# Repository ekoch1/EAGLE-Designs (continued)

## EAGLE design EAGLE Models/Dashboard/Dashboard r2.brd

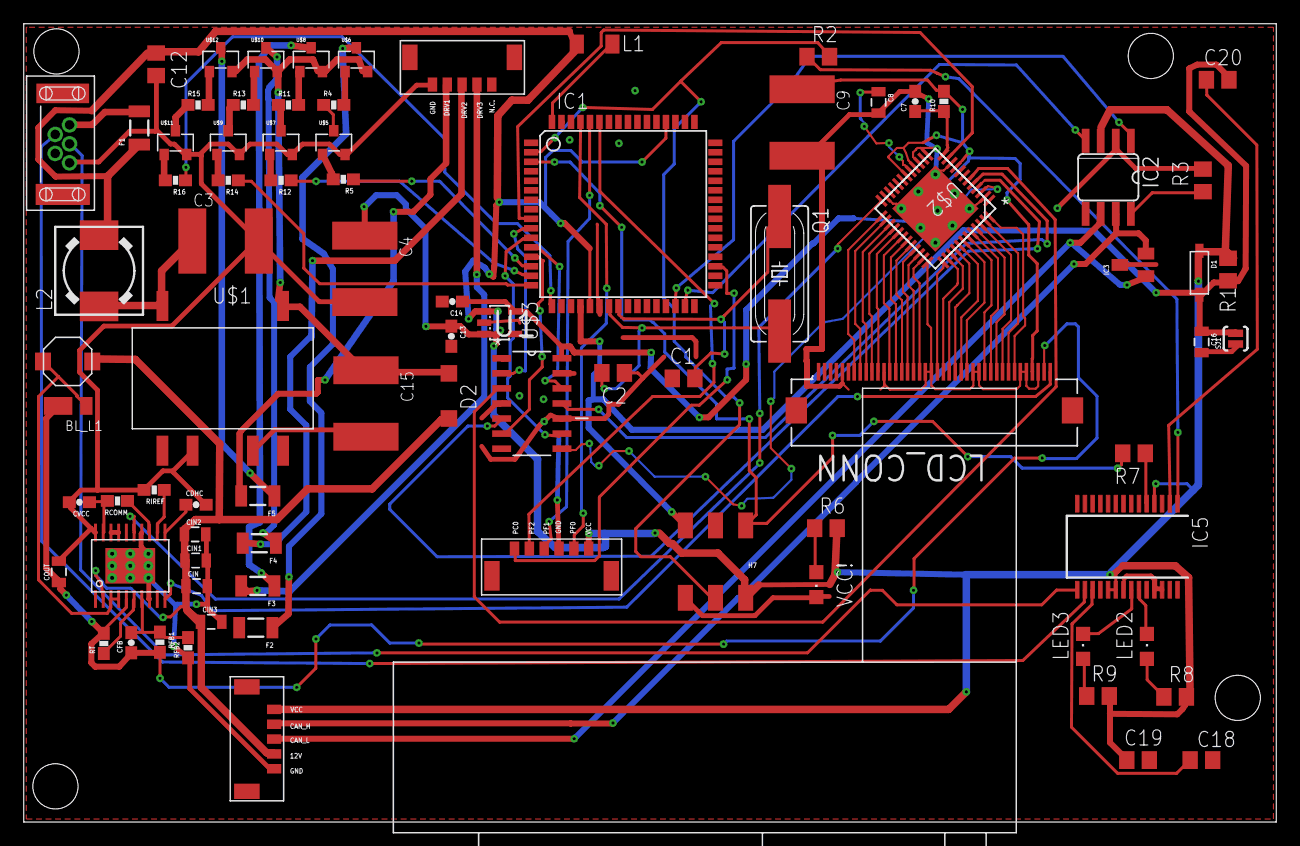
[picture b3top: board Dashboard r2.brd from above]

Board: 2 copper layers, 105.5 x 67.2 mm, 84 parts (0 on the bottom side), 100 nets.

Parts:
BL_D1: DFLS1100-7; POWERDI-123
BL_L1: 47uH; 2-SMD
C1, C2: 18pF; C0805
C3, C4: 22uF; C2220
C7: 100nF; 0603-CAP
C8: 4.7uF; 0805
C9, C15: 10uF; C2220
C12, C18, C19, C20: 100n; C0805
C13, C14: 1uF; 0603-CAP
C16: 4.7nF; 0805
CANPWR: MICRO5LOCK
CDHC: 390nF; 0603-CAP
CFB: 10.0pF; 0603-CAP
CIN, CIN1, CIN2, CIN3: 4.7uF; 0805
COUT: 120nF; 0805
CVCC: 1uF; 0603-CAP
D1: 1N4148; SOD-123
D2: 1N5819; SOD123
F1: 16V,0.25A; PTC-1206
F2, F3, F4, F5: 15V,0.5A; PTC-1206
H7: ICSP; 2X3_SMD_FCI_54202-G30
IC1: AT90CAN128; TQFP64
IC2: MCP2551SO8; SO08
IC3: NUP2105L; SOT-23
IC5: FT232RL; SSOP28
L1: CS321613-100K; L3216C
L2: 22uH; DR73
LCD_CONN: FH12A-40S-0.5SH(55); HIROSE_FH12A-40S-0.5SH(55)
LED2: RX; CHIPLED_0805
LED3: TX; CHIPLED_0805
LEDOUT: MICRO5LOCK
Q1: 56P2859; HC49UP
R1, R3: 100K; R0805
R2, R7, R8, R9: 1k; R0805
R4, R5, R11, R12, R13, R14, R15, R16: 0603-RES
R6: 1K; R0805
R10: 47k; 0603-RES
RCOMM: 52.3k; 0603-RES
RFB1: 309k; 0603-RES
RFB2: 16.2k; 0603-RES
RIREF: 20.5k; 0603-RES
ROT/PUSH: MICRO6LOCK
RT: 226k; 0603-RES
SJ1: SOLDERJUMPERNO; SJ_2S-NO
U1: 74LCX125M; SOIC127P600X175-14N
U$1: V7805-1000; V78XX-1000
U$2: FT801; RGZ48_5P15X5P15
U$3: LP5907-3.3; SOT23-DBV
U$4: LM3492HC; PWP0020A
U$5, U$7, U$9, U$11: MMBT4401-7-F; SOT-23-3
U$6, U$8, U$10, U$12: MMBT4403-7-F; SOT-23-3
U$13: TCG043WQLBAANN-GN00; TCG043WQLBAANN
U$14: MUSBB
VCC!: PWR; CHIPLED_0805

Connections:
3.3V: C9.1, C14.1, LCD_CONN.P4, R10.2, U1.14, U$2.9, U$2.16, U$2.18, U$3.5
12V: BL_L1.1, CANPWR.P2, CIN.1, CIN1.1, CIN2.1, CIN3.1, D2.A, U$4.2
12V_PROTECTED: C15.1, D2.C, U$1.1, U$6.P$3, U$8.P$3, U$10.P$3, U$12.P$3
AVR_CS: IC1.10, U1.2
AVR_MISO: IC1.13, U1.6
AVR_MOSI: IC1.12, U1.12
AVR_SCLK: IC1.11, U1.9
B2: LCD_CONN.P23, U$2.35
B3: LCD_CONN.P24, U$2.34
B4: LCD_CONN.P25, U$2.33
B5: LCD_CONN.P26, U$2.32
B6: LCD_CONN.P27, U$2.31
B7: LCD_CONN.P28, U$2.30
BACKLIGHT_CTRL: U$2.24, U$4.15
BL_ANODE: BL_D1.C, CFB.1, COUT.1, LCD_CONN.P2, RFB1.2, RT.2, U$4.5
BL_CATHODE: LCD_CONN.P1, U$4.10
CAN_H: CANPWR.P4, IC2.7, IC3.2
CAN_L: CANPWR.P3, IC2.6, IC3.1
D+: IC5.15, U$14.P3
D-: IC5.16, U$14.P2
DATA_EN: LCD_CONN.P34, U$2.25
DCLK: LCD_CONN.P30, U$2.29
DISP_EN: LCD_CONN.P31, U$2.28
DRV1: F5.2, LEDOUT.P2
DRV2: F4.2, LEDOUT.P3
DRV3: F3.2, LEDOUT.P4
DTR: C20.1, IC5.2
FT801_CS_N: U1.3, U$2.6
FT801_MISO: U1.5, U$2.4
FT801_MOSI: U1.11, U$2.5
FT801_SCLK: U1.8, U$2.3
G2: LCD_CONN.P15, U$2.42
G3: LCD_CONN.P16, U$2.41
G4: LCD_CONN.P17, U$2.40
G5: LCD_CONN.P18, U$2.39
G6: LCD_CONN.P19, U$2.38
G7: LCD_CONN.P20, U$2.37
GND: C1.1, C2.1, C3.2, C4.2, C7.2, C8.2, C9.2, C12.2, C13.2, C14.2, C15.2, C16.2, C18.2, C19.2, CANPWR.P1, CDHC.2, CIN.2, CIN1.2, CIN2.2, CIN3.2, COUT.2, CVCC.2, H7.6, IC1.22, IC1.53, IC1.63, IC2.2, IC3.3, IC5.7, IC5.18, IC5.21, IC5.25, IC5.26, LCD_CONN.P3, LCD_CONN.P5, LCD_CONN.P6, LCD_CONN.P13, LCD_CONN.P14, LCD_CONN.P21, LCD_CONN.P22, LCD_CONN.P29, LCD_CONN.P36, LEDOUT.P1, R3.2, RFB2.1, RIREF.2, ROT/PUSH.P4, SJ1.1, U1.1, U1.4, U1.10, U1.13, U$1.7, U$1.9, U$2.2, U$2.10, U$2.13, U$2.15, U$2.23, U$2.36, U$2.EP, U$2.V_1, U$2.V_2, U$2.V_3, U$2.V_4, U$2.V_5, U$2.V_6, U$2.V_7, U$2.V_8, U$2.V_9, U$3.2, U$4.8, U$4.14, U$4.17, U$4.18, U$4.20, U$4.EP, U$4.P$1, U$4.P$2, U$4.P$3, U$4.P$4, U$4.P$5, U$4.P$6, U$4.P$7, U$4.P$8, U$4.P$9, U$5.P$3, U$7.P$3, U$9.P$3, U$11.P$3, U$14.P5, VCC!.C
HSYNC: LCD_CONN.P32, U$2.27
INT_N: IC1.9, U$2.11
M8RXD: IC5.1, R2.1
M8TXD: IC5.5, R7.1
unnamed: C8.1, U$2.17
unnamed: C7.1, R10.1, U$2.12
unnamed: CVCC.1, RCOMM.2, U$4.19
unnamed: RCOMM.1, U$4.13
unnamed: IC2.8, R3.1
unnamed: CDHC.1, U$4.11
unnamed: BL_D1.A, BL_L1.2, U$4.3, U$4.4
unnamed: R6.1, VCC!.A
unnamed: CFB.2, RFB1.1, RFB2.2, U$4.7
unnamed: C1.2, IC1.24, Q1.1
unnamed: RT.1, U$4.6
unnamed: C3.1, L2.1, U$1.5
unnamed: RIREF.1, U$4.12
unnamed: IC1.64, L1.2
unnamed: R5.2, U$5.P$2
unnamed: R4.2, U$6.P$2
unnamed: R4.1, U$5.P$1
unnamed: F2.1, U$6.P$1
unnamed: R12.2, U$7.P$2
unnamed: R11.2, U$8.P$2
unnamed: R11.1, U$7.P$1
unnamed: F3.1, U$8.P$1
unnamed: R14.2, U$9.P$2
unnamed: IC5.23, LED2.C
unnamed: R13.2, U$10.P$2
unnamed: IC5.22, LED3.C
unnamed: LED2.A, R8.1
unnamed: LED3.A, R9.1
unnamed: R13.1, U$9.P$1
unnamed: F4.1, U$10.P$1
unnamed: R16.2, U$11.P$2
unnamed: R15.2, U$12.P$2
unnamed: R15.1, U$11.P$1
unnamed: F5.1, U$12.P$1
PB4(PWM): IC1.14, R5.1
PB5(PWM): IC1.15, R12.1
PB6(PWM): IC1.16, R14.1
PB7(PWM): IC1.17, R16.1
PC0: IC1.35, ROT/PUSH.P1
PF0: IC1.61, ROT/PUSH.P5
PF1: IC1.60, ROT/PUSH.P3
PF2: IC1.59, ROT/PUSH.P2
R2: LCD_CONN.P7, U$2.48
R3: LCD_CONN.P8, U$2.47
R4: LCD_CONN.P9, U$2.46
R5: LCD_CONN.P10, U$2.45
R6: LCD_CONN.P11, U$2.44
R7: LCD_CONN.P12, U$2.43
RESET: C16.1, C20.2, D1.A, H7.5, IC1.20, R1.1, SJ1.2
RX: H7.4, IC1.2, R2.2
RXCAN: IC1.31, IC2.4
TX: H7.1, IC1.3, R7.2
TXCAN: IC1.30, IC2.1
USB_V_IN: F1.2, U$14.P1
VCC: C4.1, C12.1, C13.1, C19.1, CANPWR.P5, D1.C, F1.1, H7.2, IC1.21, IC1.52, IC2.3, IC5.4, IC5.19, IC5.20, L1.1, L2.2, R1.2, R6.2, R8.2, R9.2, ROT/PUSH.P6, U$3.1, U$3.3
VCC3O: C18.1, IC5.17
VSYNC: LCD_CONN.P33, U$2.26
XTAL1: C2.2, IC1.23, Q1.2

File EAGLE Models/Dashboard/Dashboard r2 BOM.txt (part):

Partlist exported from C:/Users/Daniel Baron/Desktop/FSAE2016Boards and Schematics/Dashboard12-12.sch at 1/12/2016 12:52 PM

Part     Value               Device              Package                    Description                                                                         MPN                 OC_FARNELL OC_NEWARK PACKAGE                           SUPPLIER 
BL_D1    DFLS1100-7          DFLS1100-7          POWERDI-123                                                                                                                                                                                        
BL_L1    47uH                LTF4022-D           2-SMD                      LTF4022                                                                                                                                                                 
C1       18pF                C-USC0805           C0805                      CAPACITOR, American symbol                                                                                                                                              
C2       18pF                C-USC0805           C0805                      CAPACITOR, American symbol                                                                                                                                              
C3       22uF                C-USC2220           C2220                      CAPACITOR, American symbol                                                                                                                                              
C4       22uF                C-USC2220           C2220                      CAPACITOR, American symbol                                                                                                                                              
C7       100nF               CAP0603-CAP         0603-CAP                   Capacitor                                                                                                                                                               
C8       4.7uF               CAP0805             0805                       Capacitor                                                                                                                                                               
C9       10uF                C-USC2220           C2220                      CAPACITOR, American symbol                                                                                                                                              
C12      100n                C-USC0805           C0805                      CAPACITOR, American symbol                                                                                                                                              
C13      1uF                 CAP0603-CAP         0603-CAP                   Capacitor                                                                                                                                                               
C14      1uF                 CAP0603-CAP         0603-CAP                   Capacitor                                                                                                                                                               
C15      10uF                C-USC2220           C2220                      CAPACITOR, American symbol                                                                                                                                              
C16      4.7nF               CAP0805             0805                       Capacitor                                                                                                                                                               
C18      100n                C-USC0805           C0805                      CAPACITOR, American symbol                                                                                                                                              
C19      100n                C-USC0805           C0805                      CAPACITOR, American symbol                                                                                                                                              
C20      100n                C-USC0805           C0805                      CAPACITOR, American symbol                                                                                                                                              
CANPWR   MICRO5LOCK          MICRO5LOCK          MICRO5LOCK                                                                                                                                                                                         
CDHC     390nF               CAP0603-CAP         0603-CAP                   Capacitor                                                                                                                                                               
CFB      10.0pF              CAP0603-CAP         0603-CAP                   Capacitor                                                                                                                                                               
CIN      4.7uF               CAP0805             0805                       Capacitor                                                                                                                                                               
CIN1     4.7uF               CAP0805             0805                       Capacitor                                                                                                                                                               
CIN2     4.7uF               CAP0805             0805                       Capacitor                                                                                                                                                               
CIN3     4.7uF               CAP0805             0805                       Capacitor                                                                                                                                                               
COUT     120nF               CAP0805             0805                       Capacitor                                                                                                                                                               
CVCC     1uF                 CAP0603-CAP         0603-CAP                   Capacitor                                                                                                                                                               
D1       1N4148              DIODESOD-123        SOD-123                    Diode                                                                                                                                                                   
D2       1N5819              1N5819-BSOD123      SOD123                     1.0A SCHOTTKY BARRIER RECTIFIER                                                                                                                                         
F1       16V,0.25A           PTCSMD              PTC-1206                   Resettable Fuse PTC                                                                                                                                                     
F2       15V,0.5A            PTCSMD              PTC-1206                   Resettable Fuse PTC                                                                                                                                                     
F3       15V,0.5A            PTCSMD              PTC-1206                   Resettable Fuse PTC                                                                                                                                                     
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
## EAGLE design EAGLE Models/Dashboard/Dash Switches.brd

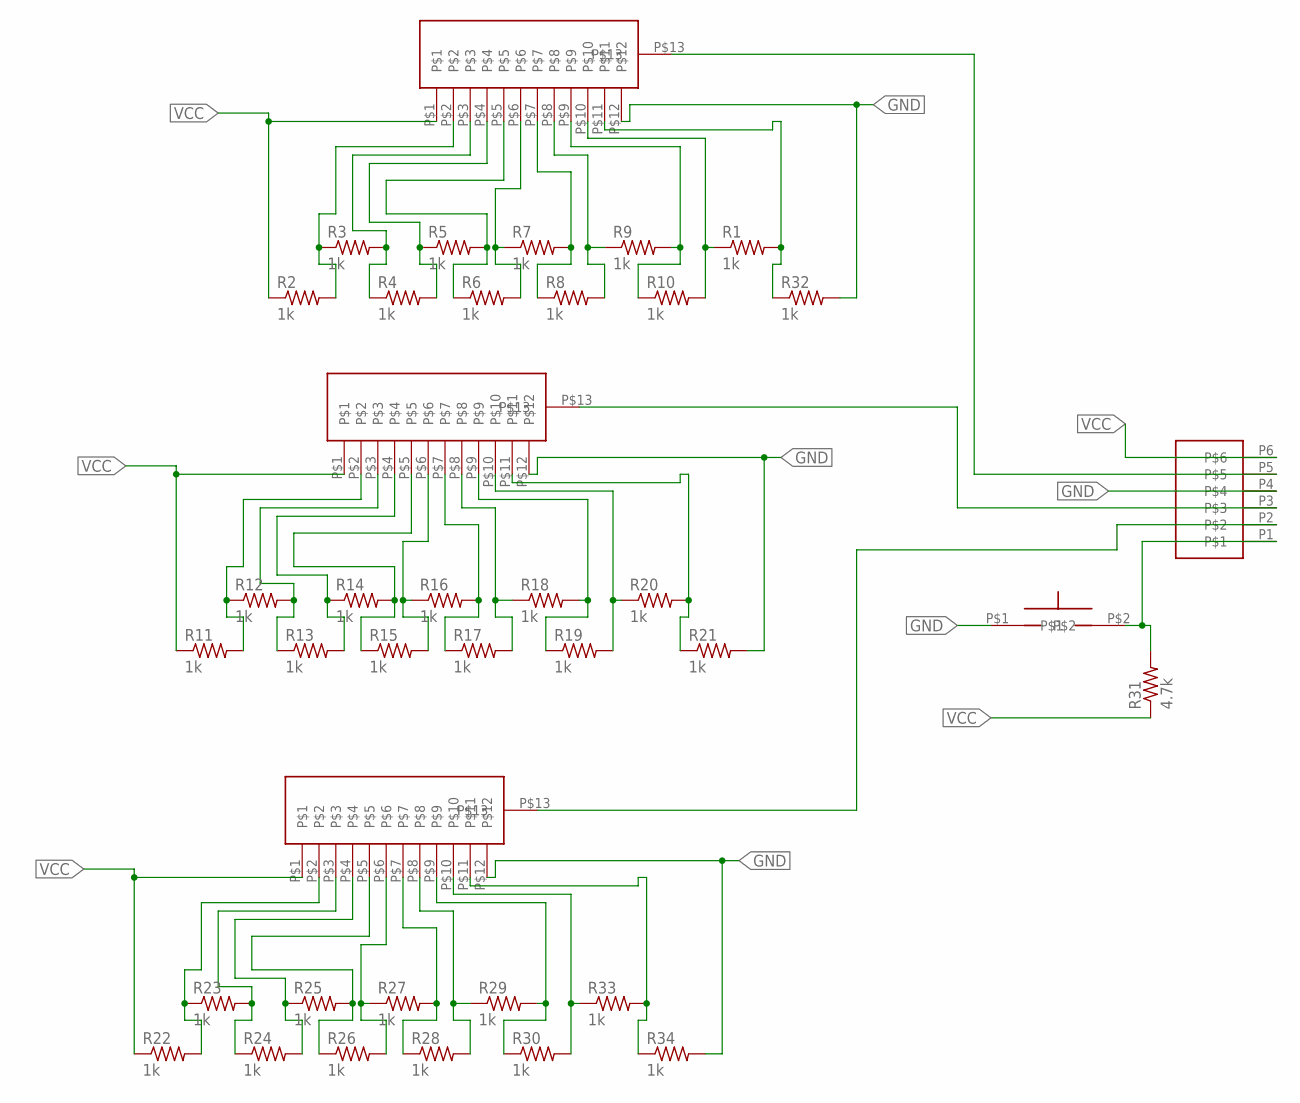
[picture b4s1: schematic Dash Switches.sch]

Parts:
R1, R2, R3, R4, R5, R6, R7, R8, R9, R10, R11, R12, R13, R14, R15, R16, R17, R18, R19, R20, R21, R22, R23, R24, R25, R26, R27, R28, R29, R30, R32, R33, R34: 1k; R0603
R31: 4.7k; R0603
U$1, U$2, U$3: ROTSWITCH
U$5: PUSH
U$6: MICRO6LOCK

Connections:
GND: R21.2, R32.2, R34.2, U$1.P$12, U$2.P$12, U$3.P$12, U$5.P$1, U$6.P4
unnamed: R1.1, R10.2, U$1.P$10
unnamed: R2.2, R3.1, U$1.P$2
unnamed: R3.2, R4.1, U$1.P$3
unnamed: R4.2, R5.1, U$1.P$4
unnamed: R5.2, R6.1, U$1.P$5
unnamed: R11.2, R12.1, U$2.P$2
unnamed: R12.2, R13.1, U$2.P$3
unnamed: R8.2, R9.1, U$1.P$8
unnamed: R9.2, R10.1, U$1.P$9
unnamed: R13.2, R14.1, U$2.P$4
unnamed: R6.2, R7.1, U$1.P$6
unnamed: R7.2, R8.1, U$1.P$7
unnamed: R14.2, R15.1, U$2.P$5
unnamed: R17.2, R18.1, U$2.P$8
unnamed: R18.2, R19.1, U$2.P$9
unnamed: R15.2, R16.1, U$2.P$6
unnamed: R16.2, R17.1, U$2.P$7
unnamed: R19.2, R20.1, U$2.P$10
unnamed: U$2.P$13, U$6.P3
unnamed: R20.2, R21.1, U$2.P$11
unnamed: R22.2, R23.1, U$3.P$2
unnamed: R23.2, R24.1, U$3.P$3
unnamed: R24.2, R25.1, U$3.P$4
unnamed: R25.2, R26.1, U$3.P$5
unnamed: R28.2, R29.1, U$3.P$8
unnamed: R29.2, R30.1, U$3.P$9
unnamed: R26.2, R27.1, U$3.P$6
unnamed: R27.2, R28.1, U$3.P$7
unnamed: R30.2, R33.1, U$3.P$10
unnamed: U$3.P$13, U$6.P2
unnamed: R33.2, R34.1, U$3.P$11
unnamed: U$1.P$13, U$6.P5
unnamed: R31.2, U$5.P$2, U$6.P1
unnamed: R1.2, R32.1, U$1.P$11
VCC: R2.1, R11.1, R22.1, R31.1, U$1.P$1, U$2.P$1, U$3.P$1, U$6.P6

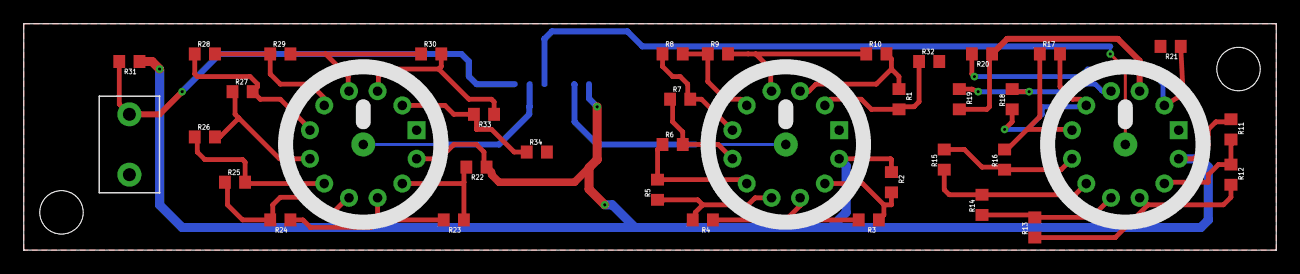
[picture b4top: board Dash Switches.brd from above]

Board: 2 copper layers, 105.4 x 19.1 mm, 39 parts (1 on the bottom side), 36 nets.

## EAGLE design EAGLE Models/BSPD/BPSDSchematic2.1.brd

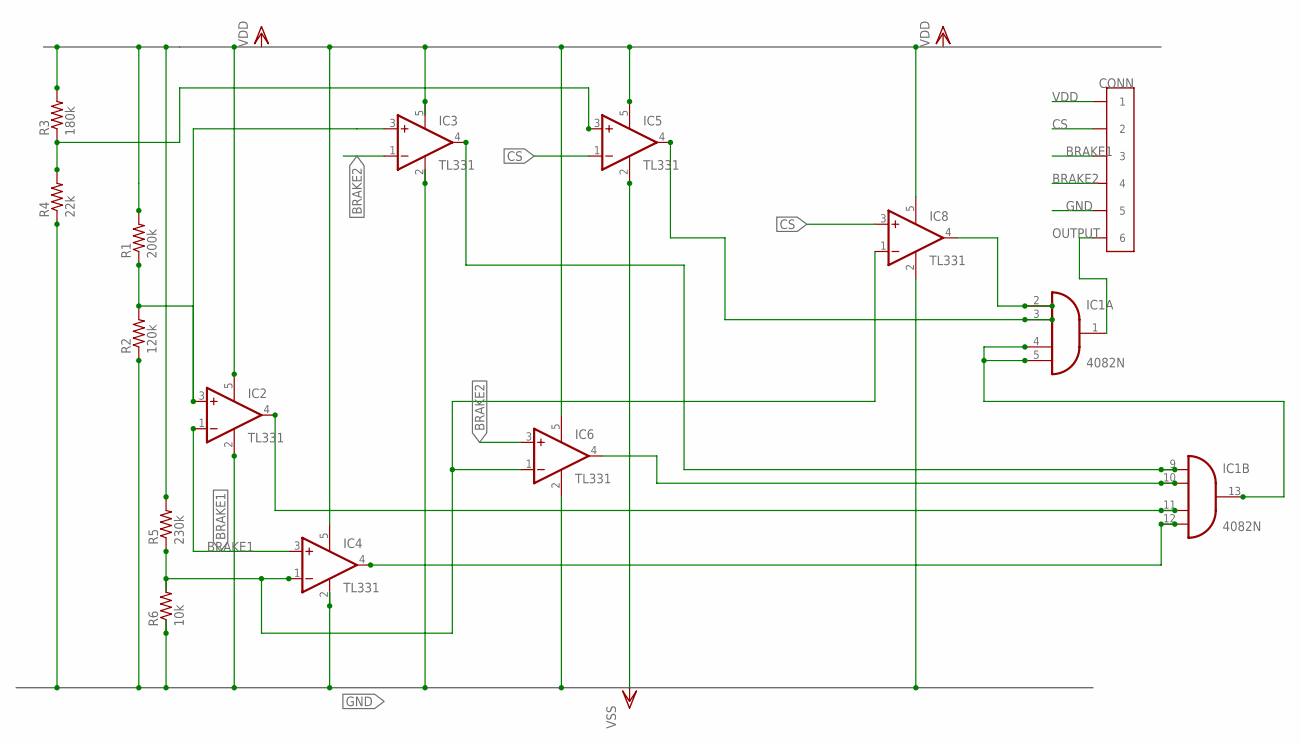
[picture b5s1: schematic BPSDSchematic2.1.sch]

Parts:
CONN: CONN_6; CONNECTOR_6
IC1: 4082N; DIL14
IC2, IC3, IC4, IC5, IC6, IC8: TL331; DBV-R-PDSO-G5
R1: 200k; 0207/15
R2: 120k; 0207/15
R3: 180k; 0207/15
R4: 22k; 0207/15
R5: 230k; 0207/15
R6: 10k; 0207/15

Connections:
BRAKE1: CONN.5 (3), CONN.6 (3), IC2.1 (-IN), IC4.3 (+IN)
BRAKE2: CONN.7 (4), CONN.8 (4), IC3.1 (-IN), IC6.3 (+IN)
CS: CONN.3 (2), CONN.4 (2), IC5.1 (-IN), IC8.3 (+IN)
GND: CONN.9 (5), CONN.10 (5), IC1.7 (VSS), IC2.2 (GND), IC3.2 (GND), IC4.2 (GND), IC5.2 (GND), IC6.2 (GND), IC8.2 (GND), R2.1, R4.1, R6.1
unnamed: IC1.12 (I3), IC4.4 (OUT)
unnamed: IC1.11 (I2), IC2.4 (OUT)
unnamed: IC1.10 (I1), IC6.4 (OUT)
unnamed: IC1.9 (I0), IC3.4 (OUT)
unnamed: IC1.2 (I0), IC8.4 (OUT)
unnamed: IC1.4 (I2), IC1.5 (I3), IC1.13 (O)
unnamed: IC2.3 (+IN), IC3.3 (+IN), R1.1, R2.2
unnamed: IC4.1 (-IN), IC6.1 (-IN), IC8.1 (-IN), R5.1, R6.2
unnamed: IC5.3 (+IN), R3.1, R4.2
unnamed: IC1.3 (I1), IC5.4 (OUT)
OUTPUT: CONN.11 (6), CONN.12 (6), IC1.1 (O)
VDD: CONN.1, CONN.2 (1), IC1.14 (VDD), IC2.5 (V+), IC3.5 (V+), IC4.5 (V+), IC5.5 (V+), IC6.5 (V+), IC8.5 (V+), R1.2, R3.2, R5.2

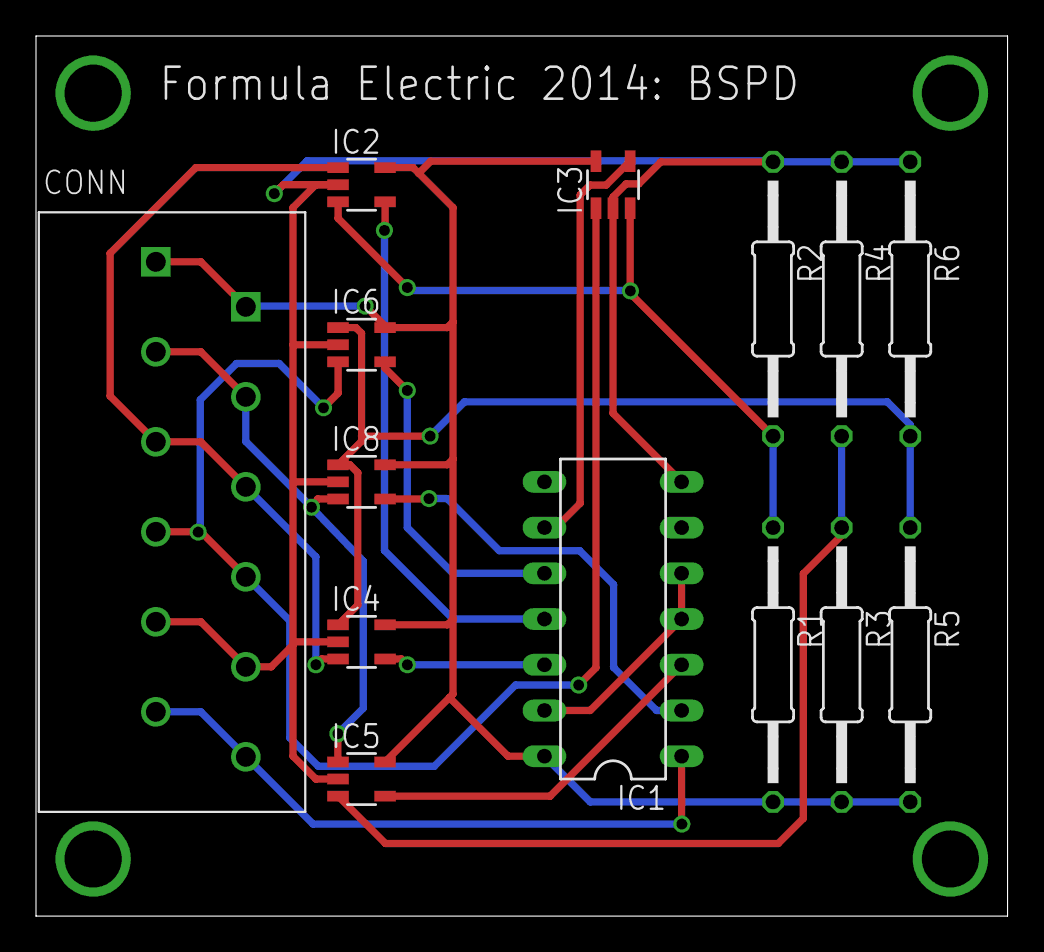
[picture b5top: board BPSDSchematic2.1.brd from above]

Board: 2 copper layers, 54.0 x 48.9 mm, 14 parts (0 on the bottom side), 16 nets.

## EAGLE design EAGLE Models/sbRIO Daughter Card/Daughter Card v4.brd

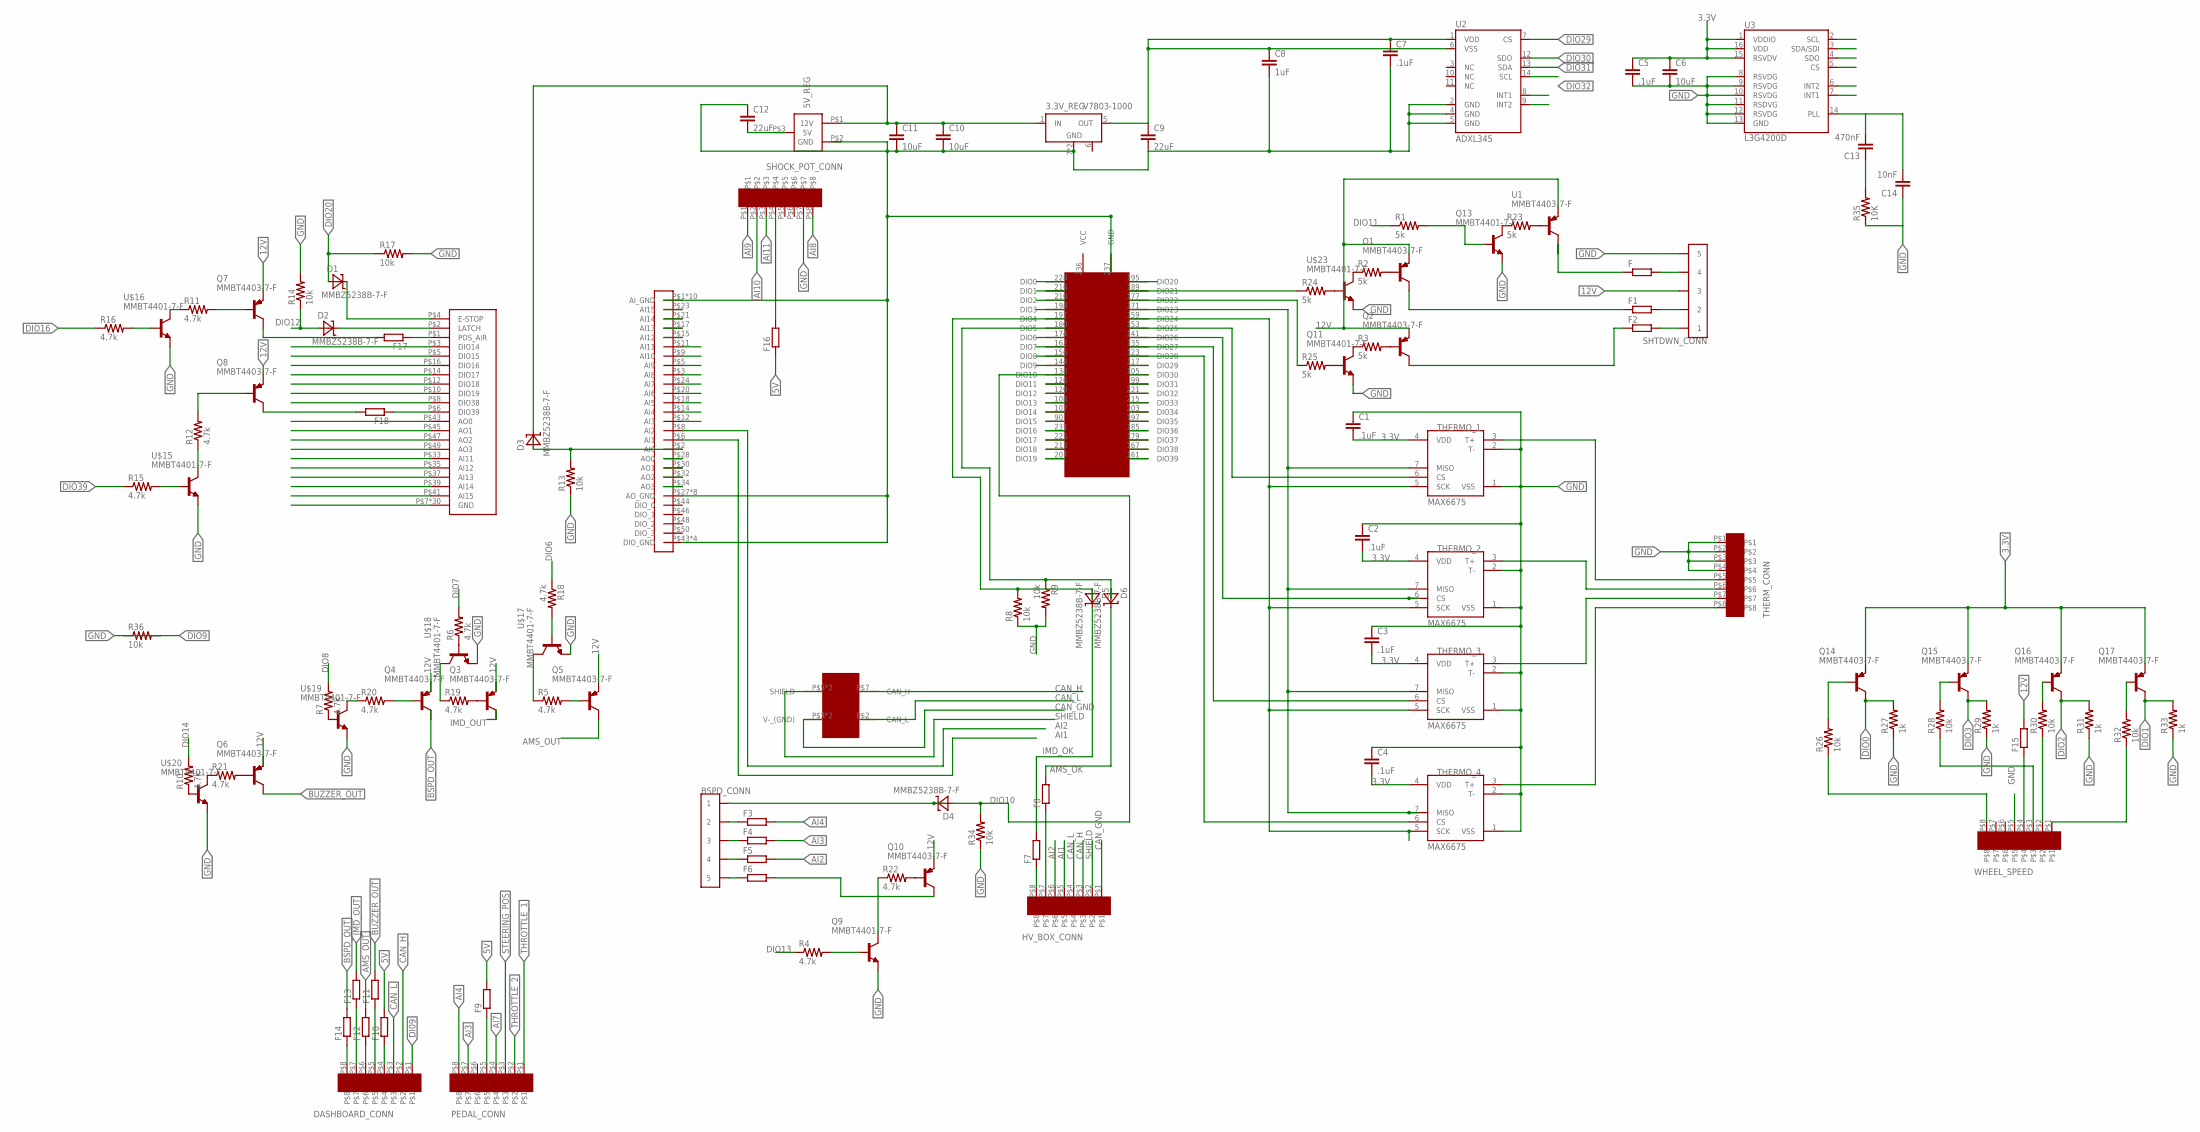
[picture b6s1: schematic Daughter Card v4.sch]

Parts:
3.3V_REG: V7803-1000; V78XX-1000
5V_REG: V78XX-1500; V78XX-1500R
BSPD_CONN: CONN_5; CONNECTOR_5
C1, C2, C3, C4, C5, C7: .1uF; 0603-CAP
C6, C10, C11: 10uF; 0603-CAP
C8: 1uF; 0603-CAP
C9, C12: 22uF; 0603-CAP
C13: 470nF; 0603-CAP
C14: 10nF; 0603-CAP
D1, D2, D3, D4, D5, D6: MMBZ5238B-7-F; SOT-23-3
DASHBOARD_CONN: EN3_PCB_8
F, F1, F2, F3, F4, F5, F6, F7, F8, F9, F10, F11, F12, F13, F14, F15, F16, F17, F18: R-EU_R0402; R0402
HV_BOX_CONN: EN3_PCB_8
PEDAL_CONN: EN3_PCB_8
Q1, Q2, Q3, Q4, Q5, Q6, Q7, Q8, Q10, Q14, Q15, Q16, Q17: MMBT4403-7-F; SOT-23-3
Q9, Q11, Q13: MMBT4401-7-F; SOT-23-3
R1, R2, R3, R23, R24, R25: 5k; R0402
R4, R5, R6, R7, R10, R11, R12, R15, R16, R18, R19, R20, R21, R22: 4.7k; R0402
R8, R9, R13, R14, R17, R26, R28, R30, R32, R34, R36: 10k; R0402
R27, R29, R31, R33: 1k; R0402
R35: 10K; 0603-RES
SBRIO_ANALOG: SBRIO_MIO; SBRIO_J502_J503
SBRIO_AUX: SBRIO_AUX; SBRIO_J502_J503
SHOCK_POT_CONN: EN3_PCB_8
SHTDWN_CONN: CONN_5; CONNECTOR_5
THERMO_1, THERMO_2, THERMO_3, THERMO_4: MAX6675; SO08
THERM_CONN: EN3_PCB_8
U1: MMBT4403-7-F; SOT-23-3
U2: ADXL345; LGA14
U3: L3G4200D; LGA16-4X4
U$2: SBRIO_W500; SBRIO_W
U$3: SBRIO_RMC; SEAM-40-XX.X-XX-06-X-A
U$15, U$16, U$17, U$18, U$19, U$20, U$23: MMBT4401-7-F; SOT-23-3
WHEEL_SPEED: EN3_PCB_8

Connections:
3.3V: 3.3V_REG.5 (OUT), C1.2, C2.2, C3.2, C4.2, C5.1, C6.1, C7.1, C8.1, C9.1, Q14.P$3 (E), Q15.P$3 (E), Q16.P$3 (E), Q17.P$3 (E), THERMO_1.4 (VDD), THERMO_2.4 (VDD), THERMO_3.4 (VDD), THERMO_4.4 (VDD), U2.1 (VDD), U2.6 (VSS), U3.1 (VDDIO), U3.15 (RSVDV), U3.16 (VDD)
5V: 5V_REG.P$3 (5V), C12.2, F9.2, F10.2, F16.1
12V: 3.3V_REG.1 (IN), 5V_REG.P$1 (12V), C10.1, C11.1, D3.P$1 (C), F15.2, Q1.P$3 (E), Q2.P$3 (E), Q3.P$3 (E), Q4.P$3 (E), Q5.P$3 (E), Q6.P$3 (E), Q7.P$3 (E), Q8.P$3 (E), Q10.P$3 (E), SHTDWN_CONN.5 (3), SHTDWN_CONN.6 (3), U1.P$3 (E)
AI1: HV_BOX_CONN.P$5, SBRIO_ANALOG.P$6 (AI1)
AI2: F5.2, HV_BOX_CONN.P$6, SBRIO_ANALOG.P$8 (AI2)
AI3: F4.2, PEDAL_CONN.P$7, SBRIO_ANALOG.P$12 (AI3)
AI4: F3.2, PEDAL_CONN.P$8, SBRIO_ANALOG.P$14 (AI4)
AI7: PEDAL_CONN.P$4, SBRIO_ANALOG.P$24 (AI7)
AI8: SBRIO_ANALOG.P$3 (AI8), SHOCK_POT_CONN.P$8
AI9: SBRIO_ANALOG.P$5 (AI9), SHOCK_POT_CONN.P$1
AI10: SBRIO_ANALOG.P$9 (AI10), SHOCK_POT_CONN.P$2
AI11: SBRIO_ANALOG.P$11 (AI11), SBRIO_AUX.P$33 (AI11), SHOCK_POT_CONN.P$3
AI12: SBRIO_ANALOG.P$15 (AI12), SBRIO_AUX.P$35 (AI12)
AI13: SBRIO_ANALOG.P$17 (AI13), SBRIO_AUX.P$37 (AI13)
AI15: SBRIO_ANALOG.P$23 (AI15), SBRIO_AUX.P$41 (AI15)
AMS_OK: D6.P$1 (C), F8.2
AMS_OUT: F12.2, Q5.P$1 (C)
AO0: SBRIO_ANALOG.P$28 (AO0), SBRIO_AUX.P$43 (AO0)
AO1: SBRIO_ANALOG.P$30 (AO1), SBRIO_AUX.P$45 (AO1)
AO2: SBRIO_ANALOG.P$32 (AO2), SBRIO_AUX.P$47 (AO2)
AO3: SBRIO_ANALOG.P$34 (AO3), SBRIO_AUX.P$49 (AO3)
BSPD_OUT: F14.2, Q4.P$1 (C)
BUZZER_OUT: F11.2, Q6.P$1 (C)
CAN_GND: HV_BOX_CONN.P$1, U$2.P$3 (V-_(GND)), U$2.P$6 (V-_(GND))
CAN_H: DASHBOARD_CONN.P$2, HV_BOX_CONN.P$3, U$2.P$7 (CAN_H)
CAN_L: DASHBOARD_CONN.P$3, HV_BOX_CONN.P$4, U$2.P$2 (CAN_L)
DI09: DASHBOARD_CONN.P$1
DIO0: Q14.P$1 (C), R27.2, U$3.228 (DIO0)
DIO1: Q17.P$1 (C), R33.2, U$3.216 (DIO1)
DIO2: Q16.P$1 (C), R31.2, U$3.210 (DIO2)
DIO3: Q15.P$1 (C), R29.2, U$3.198 (DIO3)
DIO6: R18.1, U$3.174 (DIO6)
DIO7: R6.2, U$3.162 (DIO7)
DIO8: R7.2, U$3.156 (DIO8)
DIO9: R36.2, U$3.144 (DIO9)
DIO10: D4.P$2 (A), R34.2, U$3.138 (DIO10)
DIO11: R1.1, U$3.126 (DIO11)
DIO12: D2.P$2 (A), R14.1, U$3.120 (DIO12)
DIO13: R4.1, U$3.108 (DIO13)
DIO14: R10.2, SBRIO_AUX.P$3 (DIO14), U$3.102 (DIO14)
DIO15: SBRIO_AUX.P$5 (DIO15), U$3.90 (DIO15)
DIO16: R16.1, SBRIO_AUX.P$16 (DIO16), U$3.231 (DIO16)
DIO17: SBRIO_AUX.P$14 (DIO17), U$3.225 (DIO17)
DIO18: SBRIO_AUX.P$12 (DIO18), U$3.213 (DIO18)
DIO19: SBRIO_AUX.P$10 (DIO19), U$3.207 (DIO19)
DIO20: D1.P$2 (A), R17.1, U$3.195 (DIO20)
DIO29: U2.7 (CS), U$3.117 (DIO29)
DIO30: U2.12 (SDO), U3.4 (SDO), U$3.105 (DIO30)
DIO31: U2.13 (SDA), U3.3 (SDA/SDI), U$3.99 (DIO31)
DIO32: U2.14 (SCL), U3.2 (SCL), U$3.221 (DIO32)
DIO33: U3.5 (CS), U$3.215 (DIO33)
DIO34: U3.7 (INT1), U$3.203 (DIO34)
DIO35: U3.6 (INT2), U$3.197 (DIO35)
DIO36: U2.8 (INT1), U$3.185 (DIO36)
DIO37: U2.9 (INT2), U$3.179 (DIO37)
DIO38: SBRIO_AUX.P$8 (DIO38), U$3.167 (DIO38)
DIO39: R15.1, U$3.161 (DIO39)
GND: 3.3V_REG.7 (GND), 3.3V_REG.9 (GND), 5V_REG.P$2 (GND), C1.1, C2.1, C3.1, C4.1, C5.2, C6.2, C7.2, C8.2, C9.2, C10.2, C11.2, C12.1, C14.1, Q9.P$3 (E), Q11.P$3 (E), Q13.P$3 (E), R8.1, R9.2, R13.1, R14.2, R17.2, R27.1, R29.1, R31.1, R33.1, R34.1, R35.1, R36.1, SBRIO_ANALOG.P$1 (AI_GND), SBRIO_ANALOG.P$4 (AI_GND), SBRIO_ANALOG.P$7 (AI_GND), SBRIO_ANALOG.P$10 (AI_GND), SBRIO_ANALOG.P$13 (AI_GND), SBRIO_ANALOG.P$16 (AI_GND), SBRIO_ANALOG.P$19 (AI_GND), SBRIO_ANALOG.P$22 (AI_GND), SBRIO_ANALOG.P$25 (AI_GND), SBRIO_ANALOG.P$26 (AI_GND), SBRIO_ANALOG.P$27 (AO_GND), SBRIO_ANALOG.P$29 (AO_GND), SBRIO_ANALOG.P$31 (AO_GND), SBRIO_ANALOG.P$33 (AO_GND), SBRIO_ANALOG.P$35 (AO_GND), SBRIO_ANALOG.P$37 (AO_GND), SBRIO_ANALOG.P$39 (AO_GND), SBRIO_ANALOG.P$41 (AO_GND), SBRIO_ANALOG.P$43 (DIO_GND), SBRIO_ANALOG.P$45 (DIO_GND), SBRIO_ANALOG.P$47 (DIO_GND), SBRIO_ANALOG.P$49 (DIO_GND), SBRIO_AUX.P$7 (GND), SBRIO_AUX.P$9 (GND), SBRIO_AUX.P$11 (GND), SBRIO_AUX.P$13 (GND), SBRIO_AUX.P$15 (GND), SBRIO_AUX.P$17 (GND), SBRIO_AUX.P$18 (GND), SBRIO_AUX.P$19 (GND), SBRIO_AUX.P$20 (GND), SBRIO_AUX.P$21 (GND), SBRIO_AUX.P$22 (GND), SBRIO_AUX.P$23 (GND), SBRIO_AUX.P$24 (GND), SBRIO_AUX.P$25 (GND), SBRIO_AUX.P$26 (GND), SBRIO_AUX.P$27 (GND), SBRIO_AUX.P$28 (GND), SBRIO_AUX.P$29 (GND), SBRIO_AUX.P$30 (GND), SBRIO_AUX.P$31 (GND), SBRIO_AUX.P$32 (GND), SBRIO_AUX.P$34 (GND), SBRIO_AUX.P$36 (GND), SBRIO_AUX.P$38 (GND), SBRIO_AUX.P$40 (GND), SBRIO_AUX.P$42 (GND), SBRIO_AUX.P$44 (GND), SBRIO_AUX.P$46 (GND), SBRIO_AUX.P$48 (GND), SBRIO_AUX.P$50 (GND), SHOCK_POT_CONN.P$7, SHTDWN_CONN.9 (5), SHTDWN_CONN.10 (5), THERMO_1.1 (VSS), THERMO_1.2 (T-), THERMO_2.1 (VSS), THERMO_2.2 (T-), THERMO_3.1 (VSS), THERMO_3.2 (T-), THERMO_4.1 (VSS), THERMO_4.2 (T-), THERM_CONN.P$1, THERM_CONN.P$2, THERM_CONN.P$3, THERM_CONN.P$4, U2.2 (GND), U2.4 (GND), U2.5 (GND), U3.8 (RSVDG), U3.9 (RSVDG), U3.10 (RSVDG), U3.11 (RSDVG), U3.12 (RSVDG), U3.13 (GND), U$3.237 (GND), U$15.P$3 (E), U$16.P$3 (E), U$17.P$3 (E), U$18.P$3 (E), U$19.P$3 (E), U$20.P$3 (E), U$23.P$3 (E), WHEEL_SPEED.P$5
IMD_OK: D5.P$1 (C), F7.2
IMD_OUT: F13.2, Q3.P$1 (C)
unnamed: D2.P$1 (C), SBRIO_AUX.P$2 (LATCH)
unnamed: D1.P$1 (C), SBRIO_AUX.P$4 (E-STOP)
unnamed: R32.1, WHEEL_SPEED.P$1
unnamed: D3.P$2 (A), R13.2, SBRIO_ANALOG.P$2 (AI0)
unnamed: Q6.P$2 (B), R21.2
unnamed: Q16.P$2 (B), R30.2
unnamed: F1.1, Q1.P$1 (C)
unnamed: F2.1, Q2.P$1 (C)
unnamed: R28.1, WHEEL_SPEED.P$3
unnamed: R26.1, WHEEL_SPEED.P$8
unnamed: R24.1, U$3.189 (DIO21)
unnamed: R25.1, U$3.177 (DIO22)
unnamed: F8.1, HV_BOX_CONN.P$7
unnamed: F7.1, HV_BOX_CONN.P$8
unnamed: D5.P$2 (A), R8.2, U$3.192 (DIO4)
unnamed: D6.P$2 (A), R9.1, U$3.180 (DIO5)
unnamed: THERMO_1.7 (MISO), THERMO_2.7 (MISO), THERMO_3.7 (MISO), THERMO_4.7 (MISO), U$3.171 (DIO23)
unnamed: THERMO_1.5 (SCK), THERMO_2.5 (SCK), THERMO_3.5 (SCK), THERMO_4.5 (SCK), U$3.159 (DIO24)
unnamed: F16.2, SHOCK_POT_CONN.P$4
unnamed: F15.1, WHEEL_SPEED.P$4
unnamed: F9.1, PEDAL_CONN.P$5
unnamed: DASHBOARD_CONN.P$4, F10.1
unnamed: DASHBOARD_CONN.P$5, F11.1
unnamed: THERMO_1.6 (CS), U$3.153 (DIO25)
unnamed: THERMO_2.6 (CS), U$3.141 (DIO26)
unnamed: THERMO_3.6 (CS), U$3.135 (DIO27)
unnamed: THERMO_4.6 (CS), U$3.123 (DIO28)
unnamed: THERMO_1.3 (T+), THERM_CONN.P$5
unnamed: THERMO_2.3 (T+), THERM_CONN.P$6
unnamed: THERMO_3.3 (T+), THERM_CONN.P$7
unnamed: THERMO_4.3 (T+), THERM_CONN.P$8
unnamed: DASHBOARD_CONN.P$6, F12.1
unnamed: DASHBOARD_CONN.P$7, F13.1
unnamed: DASHBOARD_CONN.P$8, F14.1
unnamed: F.2, SHTDWN_CONN.7 (4), SHTDWN_CONN.8 (4)
unnamed: C13.2, C14.2, U3.14 (PLL)
unnamed: C13.1, R35.2
unnamed: F1.2, SHTDWN_CONN.3 (2), SHTDWN_CONN.4 (2)
unnamed: F2.2, SHTDWN_CONN.1, SHTDWN_CONN.2 (1)
unnamed: BSPD_CONN.9 (5), BSPD_CONN.10 (5), F6.1
unnamed: BSPD_CONN.1, BSPD_CONN.2 (1), D4.P$1 (C)
unnamed: BSPD_CONN.7 (4), BSPD_CONN.8 (4), F5.1
unnamed: F.1, U1.P$1 (C)
unnamed: F6.2, Q10.P$1 (C)
unnamed: R23.2, U1.P$2 (B)
unnamed: Q1.P$2 (B), R2.2
unnamed: Q2.P$2 (B), R3.2
unnamed: Q10.P$2 (B), R22.2
unnamed: Q5.P$2 (B), R5.2
unnamed: Q3.P$2 (B), R19.2
unnamed: BSPD_CONN.5 (3), BSPD_CONN.6 (3), F4.1
unnamed: BSPD_CONN.3 (2), BSPD_CONN.4 (2), F3.1
unnamed: Q7.P$2 (B), R11.2
unnamed: F17.1, SBRIO_AUX.P$1 (POS_AIR)
unnamed: F17.2, Q7.P$1 (C)
unnamed: F18.2, Q8.P$1 (C)
unnamed: Q8.P$2 (B), R12.2
unnamed: F18.1, SBRIO_AUX.P$6 (DIO39)
unnamed: R15.2, U$15.P$2 (B)
unnamed: R12.1, U$15.P$1 (C)
unnamed: R16.2, U$16.P$2 (B)
unnamed: R11.1, U$16.P$1 (C)
unnamed: R5.1, U$17.P$1 (C)
unnamed: R18.2, U$17.P$2 (B)
unnamed: R19.1, U$18.P$1 (C)
unnamed: R6.1, U$18.P$2 (B)
unnamed: Q4.P$2 (B), R20.2
unnamed: R20.1, U$19.P$1 (C)
unnamed: R7.1, U$19.P$2 (B)
unnamed: R21.1, U$20.P$1 (C)
unnamed: R10.1, U$20.P$2 (B)
unnamed: Q9.P$1 (C), R22.1
unnamed: Q9.P$2 (B), R4.2
unnamed: Q13.P$1 (C), R23.1
unnamed: Q13.P$2 (B), R1.2
unnamed: R2.1, U$23.P$1 (C)
unnamed: Q11.P$1 (C), R3.1
unnamed: R24.2, U$23.P$2 (B)
unnamed: Q11.P$2 (B), R25.2
unnamed: Q14.P$2 (B), R26.2
unnamed: Q15.P$2 (B), R28.2
unnamed: R30.1, WHEEL_SPEED.P$2
unnamed: Q17.P$2 (B), R32.2
SHIELD: HV_BOX_CONN.P$2, U$2.P$5 (SHIELD), U$2.P$10 (SHIELD)
STEERING_POS: PEDAL_CONN.P$3, SBRIO_ANALOG.P$21 (AI14), SBRIO_AUX.P$39 (AI14)
THROTTLE_1: PEDAL_CONN.P$1, SBRIO_ANALOG.P$18 (AI5)
THROTTLE_2: PEDAL_CONN.P$2, SBRIO_ANALOG.P$20 (AI6)
VCC: U$3.236 (VCC)
